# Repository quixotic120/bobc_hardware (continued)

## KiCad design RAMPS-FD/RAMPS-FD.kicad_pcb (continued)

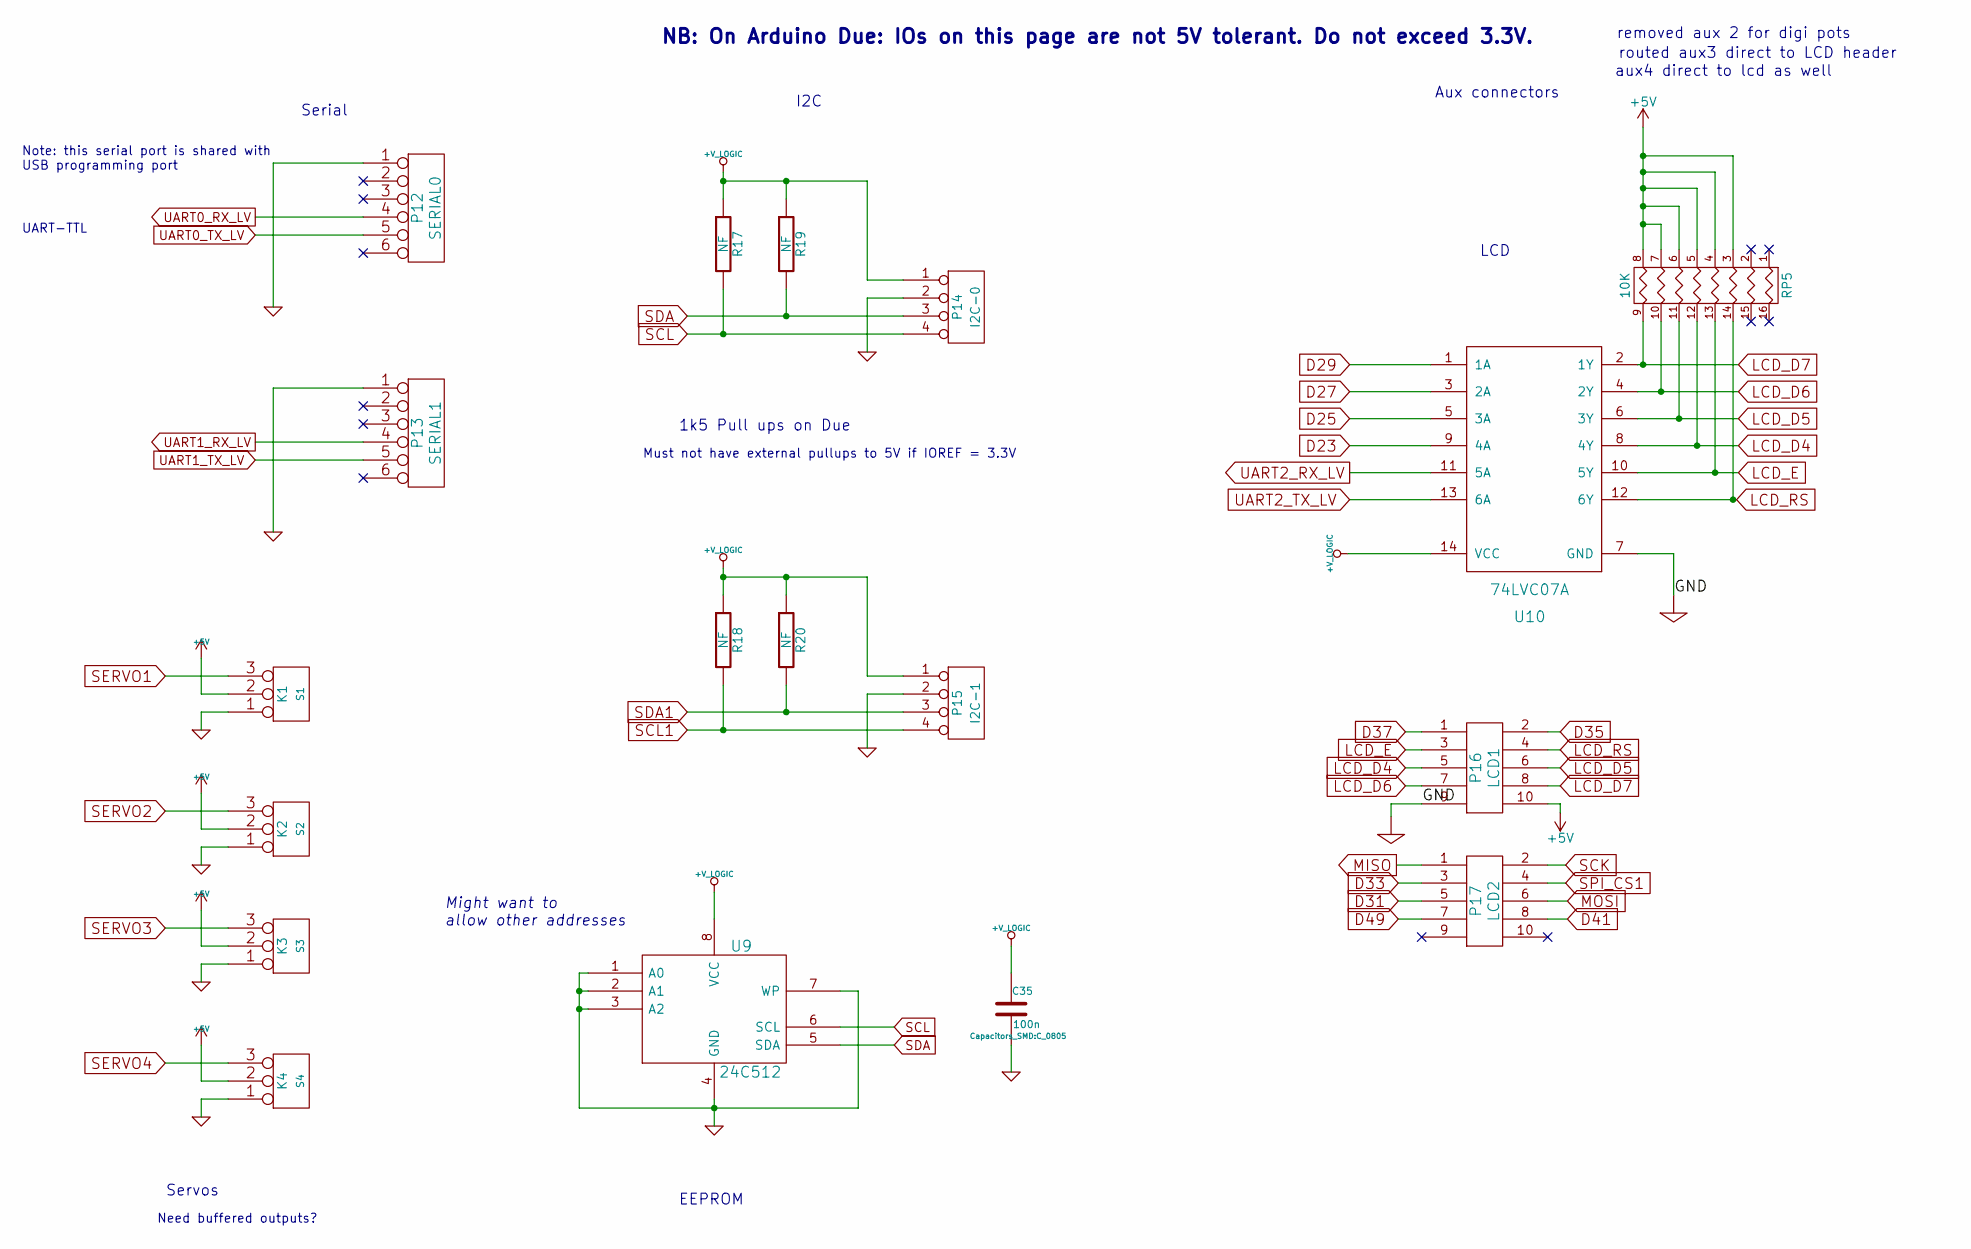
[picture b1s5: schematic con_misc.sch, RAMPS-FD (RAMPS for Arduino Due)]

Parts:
C35: 100n; C_0805
K1: S1; Pin_Header_Straight_1x03
K2: S2; Pin_Header_Straight_1x03
K3: S3; Pin_Header_Straight_1x03
K4: S4; Pin_Header_Straight_1x03
P12: SERIAL0; Pin_Header_Straight_1x06
P13: SERIAL1; Pin_Header_Straight_1x06
P14: I2C-0; Pin_Header_Straight_1x04
P15: I2C-1; Pin_Header_Straight_1x04
P16: LCD1; Pin_Header_Straight_2x05
P17: LCD2; Pin_Header_Straight_2x05
R17, R18, R19, R20: NF; R_0805
RP5: 10K; R_Cat16-8
U9: 24C512; SOIC-8-1EP_3.9x4.9mm_Pitch1.27mm
U10: 74LVC07A; TSSOP-14_4.4x5mm_Pitch0.65mm

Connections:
D23: U10.9 (4A); also elsewhere on the board
D25: U10.5 (3A); also elsewhere on the board
D27: U10.3 (2A); also elsewhere on the board
D29: U10.1 (1A); also elsewhere on the board
D31: P17.5; also elsewhere on the board
D33: P17.3; also elsewhere on the board
D35: P16.2; also elsewhere on the board
D37: P16.1; also elsewhere on the board
D41: P17.8; also elsewhere on the board
D49: P17.7; also elsewhere on the board
FD_5V: K1.2 (PM), K2.2 (PM), K3.2 (PM), K4.2 (PM), P16.10, RP5.3, RP5.4, RP5.5, RP5.6, RP5.7, RP5.8; also elsewhere on the board
LCD_D4: P16.5, RP5.12 (R5), U10.8 (4Y)
LCD_D5: P16.6, RP5.11 (R6), U10.6 (3Y)
LCD_D6: P16.7, RP5.10 (R7), U10.4 (2Y)
LCD_D7: P16.8, RP5.9 (R8), U10.2 (1Y)
LCD_E: P16.3, RP5.13 (R4), U10.10 (5Y)
LCD_RS: P16.4, RP5.14 (R3), U10.12 (6Y)
MISO: P17.1; also elsewhere on the board
MOSI: P17.6; also elsewhere on the board
SCK: P17.2; also elsewhere on the board
SCL: P14.4, R17.2, U9.6 (SCL); also elsewhere on the board
SCL1: P15.4, R18.2; also elsewhere on the board
SDA: P14.3, R19.2, U9.5 (SDA); also elsewhere on the board
SDA1: P15.3, R20.2; also elsewhere on the board
SERVO1: K1.3; also elsewhere on the board
SERVO2: K2.3; also elsewhere on the board
SERVO3: K3.3; also elsewhere on the board
SERVO4: K4.3; also elsewhere on the board
SPI_CS1: P17.4; also elsewhere on the board
UART0_RX_LV: P12.4; also elsewhere on the board
UART0_TX_LV: P12.5; also elsewhere on the board
UART1_RX_LV: P13.4; also elsewhere on the board
UART1_TX_LV: P13.5; also elsewhere on the board
UART2_RX_LV: U10.11 (5A); also elsewhere on the board
UART2_TX_LV: U10.13 (6A); also elsewhere on the board

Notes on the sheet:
Serial
UART-TTL
Need buffered outputs?
Must not have external pullups to 5V if IOREF = 3.3V
1k5 Pull ups on Due
Aux connectors
Servos
I2C
NB: On Arduino Due: IOs on this page are not 5V tolerant. Do not exceed 3.3V.
Note: this serial port is shared with USB programming port
EEPROM
Might want to allow other addresses
removed aux 2 for digi pots
routed aux3 direct to LCD header
aux4 direct to lcd as well
LCD

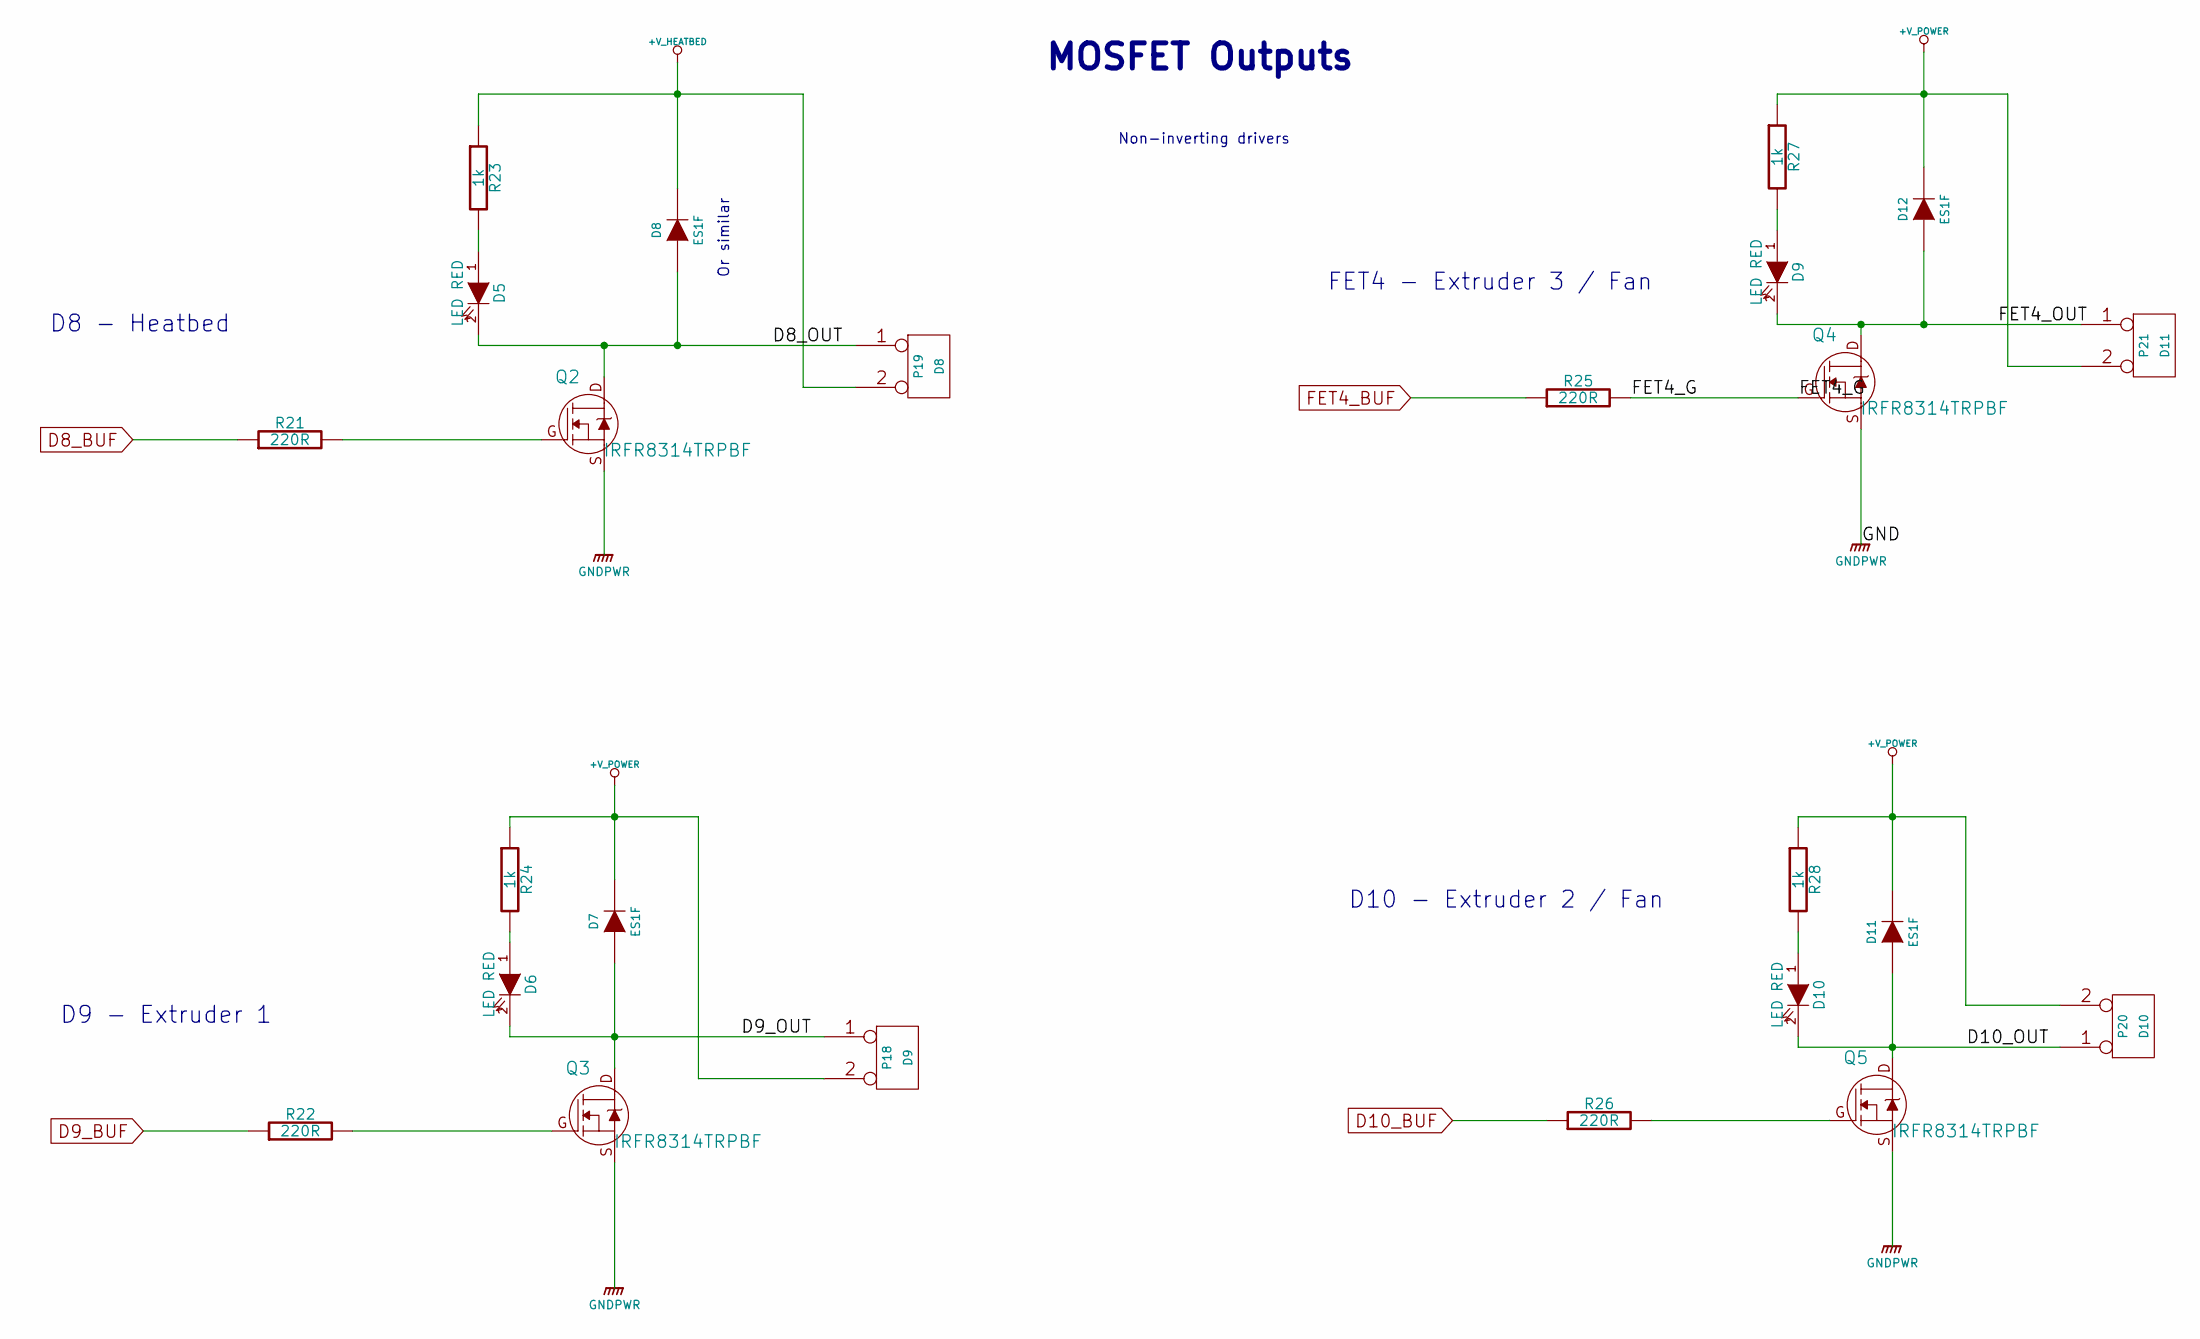
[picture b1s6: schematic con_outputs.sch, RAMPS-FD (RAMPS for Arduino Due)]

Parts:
D5, D6, D9, D10: LED RED; LED_0805
D7, D8, D11, D12: ES1F; DO-214AB
P18: D9; 2p-conn-5,08
P19: D8; 2p-conn-5,08
P20: D10; 2p-conn-5,08
P21: D11; 2p-conn-5,08
Q2, Q3, Q4, Q5: IRFR8314TRPBF; TO-252-2Lead_GDS
R21, R22, R25, R26: 220R; R_0805
R23, R24, R27, R28: 1k; R_0805

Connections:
+V_HEATBED: D8.2 (K), P19.2 (PM), R23.1; also elsewhere on the board
+V_POWER: D7.2 (K), D11.2 (K), D12.2 (K), P18.2 (PM), P20.2 (PM), P21.2 (PM), R24.1, R27.1, R28.1; also elsewhere on the board
/Mosfet Outputs/D8_OUT: D5.2 (K), D8.1 (A), P19.1, Q2.D
/Mosfet Outputs/D9_OUT: D6.2 (K), D7.1 (A), P18.1, Q3.D
/Mosfet Outputs/D10_OUT: D10.2 (K), D11.1 (A), P20.1, Q5.D
/Mosfet Outputs/FET4_G: Q4.G, R25.2
/Mosfet Outputs/FET4_OUT: D9.2 (K), D12.1 (A), P21.1, Q4.D
D8_BUF: R21.1; also elsewhere on the board
D9_BUF: R22.1; also elsewhere on the board
D10_BUF: R26.1; also elsewhere on the board
FET4_BUF: R25.1; also elsewhere on the board
unnamed: D5.1 (A), R23.2
unnamed: D6.1 (A), R24.2
unnamed: D9.1 (A), R27.2
unnamed: D10.1 (A), R28.2
unnamed: Q2.G, R21.2
unnamed: Q3.G, R22.2
unnamed: Q5.G, R26.2

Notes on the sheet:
FET4 - Extruder 3 / Fan
D10 - Extruder 2 / Fan
D9 - Extruder 1
D8 - Heatbed
Non-inverting drivers
MOSFET Outputs
Or similar

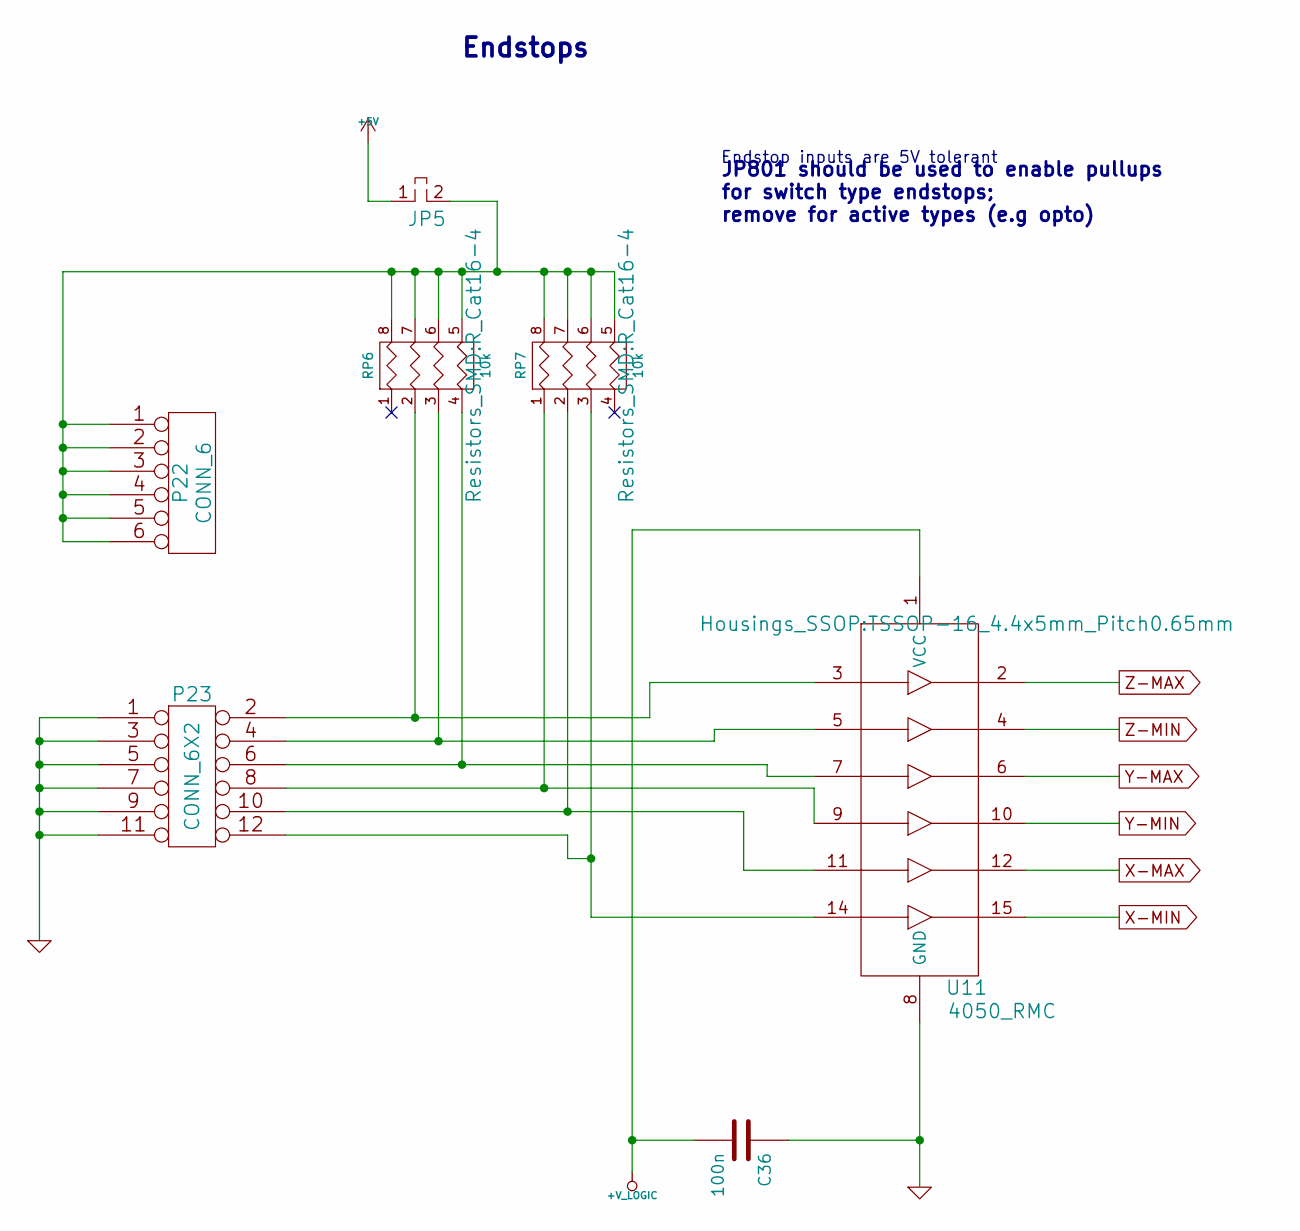
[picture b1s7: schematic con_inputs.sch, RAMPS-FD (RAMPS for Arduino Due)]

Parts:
C36: 100n; C_0805
JP5: JUMP_MINI; Pin_Header_Straight_1x02
P22: CONN_6; Pin_Header_Straight_1x06
P23: CONN_6X2; Pin_Header_Straight_2x06
RP6, RP7: 10k; R_Cat16-4
U11: 4050_RMC; TSSOP-16_4.4x5mm_Pitch0.65mm

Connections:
FD_5V: JP5.1; also elsewhere on the board
unnamed: JP5.2, P22.1, P22.2, P22.3, P22.4, P22.5, P22.6, RP6.5 (R4), RP6.6 (R3), RP6.7 (R2), RP6.8 (R1), RP7.5 (R4), RP7.6 (R3), RP7.7 (R2), RP7.8 (R1)
unnamed: P23.2, RP6.2, U11.3
unnamed: P23.4, RP6.3, U11.5
unnamed: P23.6, RP6.4, U11.7
unnamed: P23.8, RP7.1, U11.9
unnamed: P23.10, RP7.2, U11.11
unnamed: P23.12, RP7.3, U11.14
X-MAX: U11.12; also elsewhere on the board
X-MIN: U11.15; also elsewhere on the board
Y-MAX: U11.6; also elsewhere on the board
Y-MIN: U11.10; also elsewhere on the board
Z-MAX: U11.2; also elsewhere on the board
Z-MIN: U11.4; also elsewhere on the board

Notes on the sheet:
Endstop inputs are 5V tolerant
Endstops
JP801 should be used to enable pullups for switch type endstops; remove for active types (e.g opto)

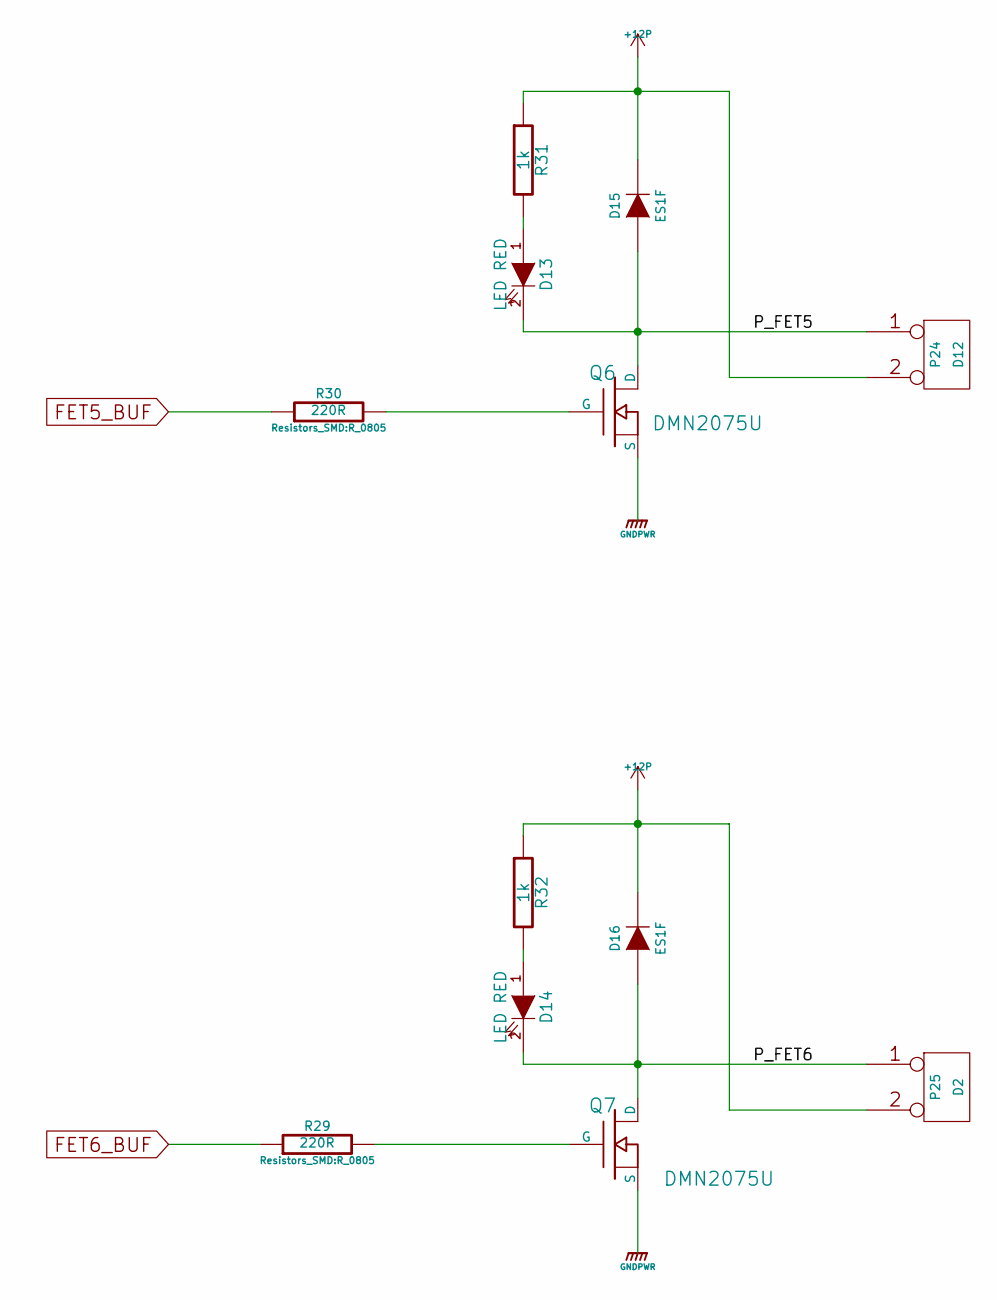
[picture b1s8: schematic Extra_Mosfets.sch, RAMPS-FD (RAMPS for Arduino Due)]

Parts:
D13, D14: LED RED; LED_0805
D15, D16: ES1F; DO-214AB
P24: D12; Socket_MOLEX-KK-RM2-54mm_Lock_2pin_straight
P25: D2; Socket_MOLEX-KK-RM2-54mm_Lock_2pin_straight
Q6, Q7: DMN2075U; SOT-23_GDS
R29, R30: 220R; R_0805
R31, R32: 1k; R_0805

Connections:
+12P: D15.2 (K), D16.2 (K), P24.2 (PM), P25.2 (PM), R31.1, R32.1; also elsewhere on the board
/Extra MOSFETs/P_FET5: D13.2 (K), D15.1 (A), P24.1, Q6.D
/Extra MOSFETs/P_FET6: D14.2 (K), D16.1 (A), P25.1, Q7.D
FET5_BUF: R30.1; also elsewhere on the board
FET6_BUF: R29.1; also elsewhere on the board
unnamed: D13.1 (A), R31.2
unnamed: D14.1 (A), R32.2
unnamed: Q6.G, R30.2
unnamed: Q7.G, R29.2

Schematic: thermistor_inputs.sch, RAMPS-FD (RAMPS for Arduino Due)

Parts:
C37, C38, C39, C40: 100n; C_0805
C41, C42, C43, C44: 10u; C_0805
C45: 10u; c_elec_4x5.3
D17, D18, D19, D20, D21, D22, D23, D24: 1N4148; SOD-323
P26: CONN_4X2; Pin_Header_Straight_2x04
R33, R34, R35, R36, R37, R39, R40, R43: 1k; R_0805
R38: 1K; R_0805
R41: 10k; R_0805
R42: 1k5; R_0805
U12: TL431_SOT23_RMC; SOT-23

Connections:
+12P: R41.1; also elsewhere on the board
GNDA: P26.1, P26.3, P26.5, P26.7; also elsewhere on the board
unnamed: P26.2, R33.2, R38.1
unnamed: P26.4, R34.2, R40.1
unnamed: P26.6, R35.2, R39.1
unnamed: P26.8, R36.2, R37.1
unnamed: R42.2, R43.1, U12.1 (R)
OV_REF: C45.1, D17.2 (K), D19.2 (K), D21.2 (K), D23.2 (K), R41.2, R42.1, U12.2 (K)
THERM0: C37.1, C41.1, D21.1 (A), D22.2 (K), R38.2; also elsewhere on the board
THERM1: C38.1, C42.1, D23.1 (A), D24.2 (K), R40.2; also elsewhere on the board
THERM2: C39.1, C43.1, D17.1 (A), D18.2 (K), R39.2; also elsewhere on the board
THERM3: C40.1, C44.1, D19.1 (A), D20.2 (K), R37.2; also elsewhere on the board

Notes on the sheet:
To CPU
From thermistor
Thermistor Inputs
Limit at 3.1V
Vref = 1.24V

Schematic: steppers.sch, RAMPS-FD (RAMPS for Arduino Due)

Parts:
C46, C50, C54, C57, C58, C61, C62, C68, C71: 100n/50v; C_0805
C47, C52, C65: 4u7/10v; C_0805
C48, C53, C66: 100u/35v; c_elec_6.3x7.7
C49, C67, C73: 100n50v; C_0805
C51, C63, C72: 470n/10v; C_0805
C55, C59, C69: 22n/50v; C_0805
C56, C60, C70: 1u/50v; C_0805
C64: 0.1u; C_0805
P27: Y-MOT; Socket_MOLEX-KK-RM2-54mm_Lock_4pin_straight
P28: Z-MOT1; Socket_MOLEX-KK-RM2-54mm_Lock_4pin_straight
P29: X-MOT; Socket_MOLEX-KK-RM2-54mm_Lock_4pin_straight
P30: Z-MOT2; Socket_MOLEX-KK-RM2-54mm_Lock_4pin_straight
P34: Y_SPRD_En; Pin_Header_Straight_1x02
P35: Z_SPRD_En; Pin_Header_Straight_1x02
P36: X_SPRD_En; Pin_Header_Straight_1x02
R44, R45, R50: 2r2; R_0805
R46, R47, R48, R49, R53, R54: 0r11; R_0805
R51, R52: 4k7; R_0805
U13, U14, U16: TMC2130; QFN-36-1EP_5x6mm_Pitch0.5mm
U15: DS3904; MSOP-8-1EP_3x3mm_Pitch0.65mm
W4: Y_REF; SolderWirePad_single_0-8mmDrill
W5: Z_REF; SolderWirePad_single_0-8mmDrill
W6: X_REF; SolderWirePad_single_0-8mmDrill
WXD7: XD0; SolderWirePad_single_0-8mmDrill
WXD8: XD1; SolderWirePad_single_0-8mmDrill
WYD1: YD0; SolderWirePad_single_0-8mmDrill
WYD2: YD1; SolderWirePad_single_0-8mmDrill
WZd0: ZD0; SolderWirePad_single_0-8mmDrill
WzD1: ZD1; SolderWirePad_single_0-8mmDrill

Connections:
+V_MOTOR: C54.2, C56.2, C57.2, C58.2, C60.2, C61.2, C68.2, C70.2, C71.2, U13.16 (VS), U13.31 (VS), U14.16 (VS), U14.31 (VS), U16.16 (VS), U16.31 (VS); also elsewhere on the board
/X_EN_BUF: U16.22 (DRV_ENN_CFG6); also elsewhere on the board
/Y_EN_BUF: U13.22 (DRV_ENN_CFG6); also elsewhere on the board
/Z_EN_BUF: U14.22 (DRV_ENN_CFG6); also elsewhere on the board
FD_5V: C64.1, R51.2, R52.1, U15.3 (VCC); also elsewhere on the board
unnamed: C46.2, U13.8 (VCC_IO)
unnamed: C47.1, R44.1, U13.25 (5VOUT)
unnamed: C48.1, C49.2, U13.30 (VSA)
unnamed: C50.2, U14.8 (VCC_IO)
unnamed: C51.1, R45.2, U14.19 (ENCA_DCIN_CFG5), U14.26 (VCC)
unnamed: C52.1, R45.1, U14.25 (5VOUT)
unnamed: C53.1, C73.2, U14.30 (VSA)
unnamed: C55.1, U13.28 (CPI)
unnamed: C55.2, U13.27 (CPO)
unnamed: C57.1, U13.29 (VCP)
unnamed: C59.1, U14.28 (CPI)
unnamed: C59.2, U14.27 (CPO)
unnamed: C61.1, U14.29 (VCP)
unnamed: C62.2, U16.8 (VCC_IO)
unnamed: C63.1, R50.2, U16.19 (ENCA_DCIN_CFG5), U16.26 (VCC)
unnamed: C65.1, R50.1, U16.25 (5VOUT)
unnamed: C66.1, C67.2, U16.30 (VSA)
unnamed: C69.1, U16.28 (CPI)
unnamed: C69.2, U16.27 (CPO)
unnamed: C71.1, U16.29 (VCP)
unnamed: C72.1, R44.2, U13.19 (ENCA_DCIN_CFG5), U13.26 (VCC)
unnamed: P27.1, U13.15 (OB2)
unnamed: P27.2, U13.32 (OA2)
unnamed: P27.3, U13.34 (OA1)
unnamed: P27.4, U13.13 (OB1)
unnamed: P28.1, P30.1, U14.15 (OB2)
unnamed: P28.2, P30.2, U14.32 (OA2)
unnamed: P28.3, P30.3, U14.34 (OA1)
unnamed: P28.4, P30.4, U14.13 (OB1)
unnamed: P29.1, U16.15 (OB2)
unnamed: P29.2, U16.32 (OA2)
unnamed: P29.3, U16.34 (OA1)
unnamed: P29.4, U16.13 (OB1)
unnamed: P34.1, U13.4 (SDI_NAI_CFG1)
unnamed: P35.1, U14.4 (SDI_NAI_CFG1)
unnamed: P36.1, U16.4 (SDI_NAI_CFG1)
unnamed: R46.1, U13.14 (BRB)
unnamed: R47.1, U13.33 (BRA)
unnamed: R48.1, U14.14 (BRB)
unnamed: R49.1, U14.33 (BRA)
unnamed: R53.1, U16.14 (BRB)
unnamed: R54.1, U16.33 (BRA)
unnamed: U13.20 (SWN_DIAG0), WYD1.1
unnamed: U13.21 (SWP_DIAG1), WYD2.1
unnamed: U14.20 (SWN_DIAG0), WZd0.1
unnamed: U14.21 (SWP_DIAG1), WzD1.1
unnamed: U16.20 (SWN_DIAG0), WXD7.1
unnamed: U16.21 (SWP_DIAG1), WXD8.1
SCL: R51.1, U15.2 (SCL); also elsewhere on the board
SDA: R52.2, U15.1 (SDA); also elsewhere on the board
X_DIR: U16.7 (REFR_DIR); also elsewhere on the board
X_STEP: U16.6 (REFL_STEP); also elsewhere on the board
X_TRIM: U15.7 (H0), U16.23 (AIN_IREF), W6.1
Y_DIR: U13.7 (REFR_DIR); also elsewhere on the board
Y_STEP: U13.6 (REFL_STEP); also elsewhere on the board
Y_TRIM: U13.23 (AIN_IREF), U15.6 (H1), W4.1
Z_DIR: U14.7 (REFR_DIR); also elsewhere on the board
Z_STEP: U14.6 (REFL_STEP); also elsewhere on the board
Z_TRIM: U14.23 (AIN_IREF), U15.5 (H2), W5.1

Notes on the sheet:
X AXIS
Y AXIS
Z AXIS

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
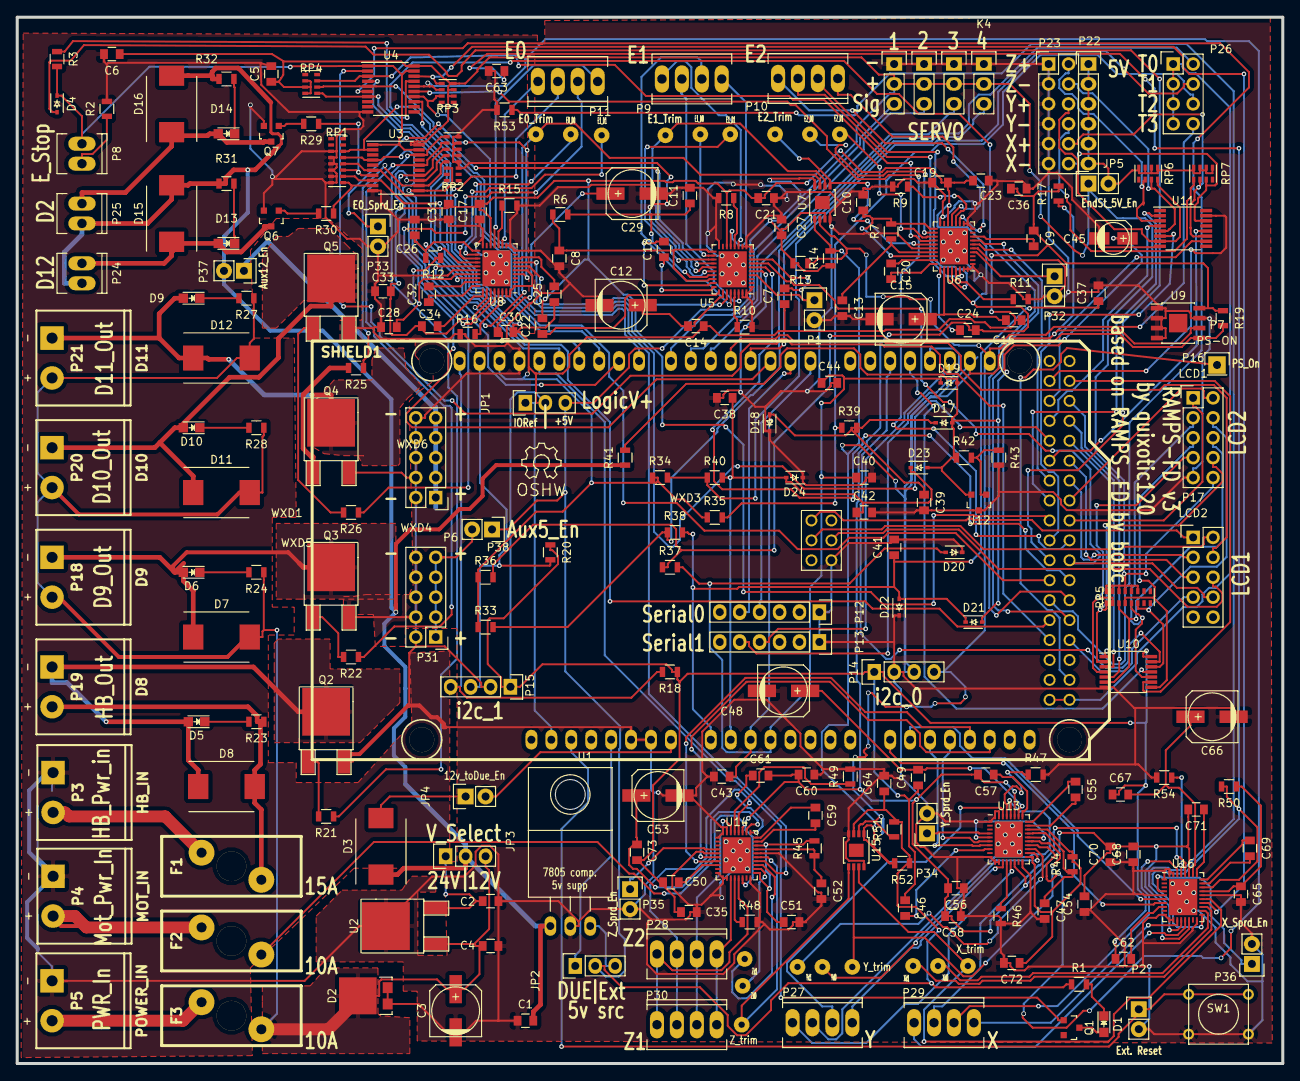
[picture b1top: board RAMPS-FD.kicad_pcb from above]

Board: 2 copper layers, 161.3 x 133.3 mm, 250 parts (0 on the bottom side), 239 nets.

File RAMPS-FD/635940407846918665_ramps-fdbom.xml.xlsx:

Reference | Value | Footprint | Count | Note
SHIELD1 | ARDUINO_DUE_SHIELD | arduinodue:ARDUINO_DUE_RAMPS_SHIELD | 1
SW1 | RESET | Buttons_Switches_ThroughHole:SW_PUSH_SMALL | 1
D1 | LED GRN | LEDs:LED_0805 | 1
R1 | 330R | Resistors_SMD:R_0805 | 1
P2 | RESET | Pin_Headers:Pin_Header_Straight_1x02 | 1
Q1 | 2N7002 | TO_SOT_Packages_SMD:SOT-23_GDS | 1
LOGO1 | OPEN_HARDWARE_1 | Symbols:Symbol_OSHW-Logo_SilkScreen | 1
JP3 | VSEL | Pin_Headers:Pin_Header_Straight_1x03 | 1
JP4 | VIN | Pin_Headers:Pin_Header_Straight_1x02 | 1
P5 | POWER_IN | RAMPS-FD v3:2p-conn-5,08 | 1
P3 | HB_IN | RAMPS-FD v3:2p-conn-5,08 | 1
JP1 | VLOG | Pin_Headers:Pin_Header_Straight_1x03 | 1
F2;F3 | FUSE 10A | RAMPS-FD v3:FUSE-MINI-AUTO | 2
P4 | MOT_IN | RAMPS-FD v3:2p-conn-5,08 | 1
P7 | PS-ON | Pin_Headers:Pin_Header_Straight_1x01 | 1
C4 | 100n 35V | Capacitors_SMD:C_0805 | 1
C3 | 100u 35V | Capacitors_SMD:c_elec_6.3x7.7 | 1
D3;D8;D12;D7;D11;D15;D16 | ES1F | Diodes_SMD:DO-214AB | 7
F1 | FUSE 15A | RAMPS-FD v3:FUSE-MINI-AUTO | 1
U2 | LM7812 | TO_SOT_Packages_THT:TO-252-2Lead_edit | 1
C2 | 100n 16V | Capacitors_SMD:C_0805 | 1
D2 | SS10Pxx | TO_SOT_Packages_SMD:TO-277A | 1 | If = 10 A
U1 | oki-78sr-5h | TO_SOT_Packages_THT:TO-220_Neutral123_Horizontal_OKI_Mod | 1
C1 | 22u/35v | Capacitors_SMD:C_0805 | 1
P31 | 5v aux | Pin_Headers:Pin_Header_Straight_2x05 | 1
P6 | 12V aux | Pin_Headers:Pin_Header_Straight_2x05 | 1
JP2 | 5V_SEL | Pin_Headers:Pin_Header_Straight_1x03 | 1
U4;U3 | 74ACT244 | Housings_SSOP:TSSOP-20_4.4x6.5mm_Pitch0.65mm | 2
C6;C5;C35;C36;C37;C38;C39;C40 | 100n | Capacitors_SMD:C_0805 | 8
D4;D22;D21;D23;D24;D18;D17;D19;D20 | 1N4148 | Diodes_SMD:SOD-323 | 9
R2;R13;R14;R51;R52 | 4k7 | Resistors_SMD:R_0805 | 5
P8 | ESTOP | Sockets_MOLEX_KK-System:Socket_MOLEX-KK-RM2-54mm_Lock_2pin_straight | 1
R3 | 100k | Resistors_SMD:R_0805 | 1
RP1;RP2 | R_PACK8 | Resistors_SMD:R_Cat16-8 | 2
RP4;RP3 | R_PACK4 | Resistors_SMD:R_Cat16-4 | 2
P11 | E0-MOT | Sockets_MOLEX_KK-System:Socket_MOLEX-KK-RM2-54mm_Lock_4pin_straight | 1
U8;U5;U6;U16;U13;U14 | TMC2130 | Housings_DFN_QFN:QFN-36-1EP_5x6mm_Pitch0.5mm | 6
C31;C34;C25;C17;C22;C7;C19;C24;C9;C68;C71;C62;C54;C57;C46;C58;C61;C50 | 100n/50v | Capacitors_SMD:C_0805 | 18
C33;C21;C23;C70;C56;C60 | 1u/50v | Capacitors_SMD:C_0805 | 6
C32;C18;C20;C69;C55;C59 | 22n/50v | Capacitors_SMD:C_0805 | 6
R16;R15;R10;R8;R11;R9;R54;R53;R47;R46;R49;R48 | 0r11 | Resistors_SMD:R_0805 | 12
R12;R6;R7;R50;R44;R45 | 2r2 | Resistors_SMD:R_0805 | 6
C30;C14;C16;C67;C49;C73 | 100n50v | Capacitors_SMD:C_0805 | 6
C28;C11;C13;C65;C47;C52 | 4u7/10v | Capacitors_SMD:C_0805 | 6
C26;C8;C10;C63;C72;C51 | 470n/10v | Capacitors_SMD:C_0805 | 6
C29;C12;C15;C66;C48;C53 | 100u/35v | Capacitors_SMD:c_elec_6.3x7.7 | 6
WXD6 | E0D1 | Wire_Pads:SolderWirePad_single_0-8mmDrill | 1
WXD5 | E0D0 | Wire_Pads:SolderWirePad_single_0-8mmDrill | 1
U7;U15 | DS3904 | Housings_SSOP:MSOP-8-1EP_3x3mm_Pitch0.65mm | 2
C27;C64 | 0.1u | Capacitors_SMD:C_0805 | 2
W3 | E0_REF | Wire_Pads:SolderWirePad_single_0-8mmDrill | 1
P9 | E1-MOT | Sockets_MOLEX_KK-System:Socket_MOLEX-KK-RM2-54mm_Lock_4pin_straight | 1
WXD2 | E1D1 | Wire_Pads:SolderWirePad_single_0-8mmDrill | 1
WXD1 | E1D0 | Wire_Pads:SolderWirePad_single_0-8mmDrill | 1
W1 | E1_REF | Wire_Pads:SolderWirePad_single_0-8mmDrill | 1
P10 | E2-MOT | Sockets_MOLEX_KK-System:Socket_MOLEX-KK-RM2-54mm_Lock_4pin_straight | 1
WXD4 | E2D1 | Wire_Pads:SolderWirePad_single_0-8mmDrill | 1
WXD3 | E2D0 | Wire_Pads:SolderWirePad_single_0-8mmDrill | 1
W2 | E2_REF | Wire_Pads:SolderWirePad_single_0-8mmDrill | 1
P33 | E0_SPRD_En | Pin_Headers:Pin_Header_Straight_1x02 | 1
P1 | E1_SPRD_En | Pin_Headers:Pin_Header_Straight_1x02 | 1
P32 | E2_SPRD_En | Pin_Headers:Pin_Header_Straight_1x02 | 1
P15 | I2C-1 | Pin_Headers:Pin_Header_Straight_1x04 | 1
R20;R18;R17;R19 | NF | Resistors_SMD:R_0805 | 4
P13 | SERIAL1 | Pin_Headers:Pin_Header_Straight_1x06 | 1
P12 | SERIAL0 | Pin_Headers:Pin_Header_Straight_1x06 | 1
K4 | S4 | Pin_Headers:Pin_Header_Straight_1x04 | 1
K3 | S3 | Pin_Headers:Pin_Header_Straight_1x04 | 1
K2 | S2 | Pin_Headers:Pin_Header_Straight_1x04 | 1
K1 | S1 | Pin_Headers:Pin_Header_Straight_1x04 | 1
P14 | I2C-0 | Pin_Headers:Pin_Header_Straight_1x04 | 1
U9 | 24C512 | Housings_SOIC:SOIC-8-1EP_3.9x4.9mm_Pitch1.27mm | 1
P16 | LCD1 | Pin_Headers:Pin_Header_Straight_2x05 | 1
P17 | LCD2 | Pin_Headers:Pin_Header_Straight_2x05 | 1
RP5 | 10K | Resistors_SMD:R_Cat16-8 | 1
U10;U11 | 74LVC07A | Housings_SSOP:TSSOP-14_4.4x5mm_Pitch0.65mm | 2
P20 | D10 | RAMPS-FD v3:2p-conn-5,08 | 1
P18 | D9 | RAMPS-FD v3:2p-conn-5,08 | 1
P19 | D8 | RAMPS-FD v3:2p-conn-5,08 | 1
P21 | D11 | RAMPS-FD v3:2p-conn-5,08 | 1
D9;D6;D10;D5;D13;D14 | LED RED | LEDs:LED_0805 | 6
R27;R24;R28;R23;R31;R32;R40;R39;R37;R36;R35;R34;R33;R43 | 1k | Resistors_SMD:R_0805 | 14
Q4;Q2;Q3;Q5 | IRFR8314TRPBF | TO_SOT_Packages_SMD:TO-252-2Lead_GDS | 4
R21;R22;R26;R25;R30;R29 | 220R | Resistors_SMD:R_0805 | 6
RP6;RP7 | 10k | Resistors_SMD:R_Cat16-4 | 2
JP5 | JUMP_MINI | Pin_Headers:Pin_Header_Straight_1x02 | 1
P23 | CONN_6X2 | Pin_Headers:Pin_Header_Straight_2x06 | 1
P22 | CONN_6 | Pin_Headers:Pin_Header_Straight_1x06 | 1
Q6;Q7 | DMN2075U | TO_SOT_Packages_SMD:SOT-23_GDS | 2
P24 | D12 | Sockets_MOLEX_KK-System:Socket_MOLEX-KK-RM2-54mm_Lock_2pin_straight | 1
P25 | D2 | Sockets_MOLEX_KK-System:Socket_MOLEX-KK-RM2-54mm_Lock_2pin_straight | 1
R38 | 1K | Resistors_SMD:R_0805 | 1
C44;C43;C42;C41 | 10u | Capacitors_SMD:C_0805 | 4
P26 | CONN_4X2 | Pin_Headers:Pin_Header_Straight_2x04 | 1
R41 | 10k | Resistors_SMD:R_0805 | 1
R42 | 1k5 | Resistors_SMD:R_0805 | 1
C45 | 10u | Capacitors_SMD:c_elec_4x5.3 | 1
U12 | TL431_SOT23_RMC | TO_SOT_Packages_SMD:SOT-23 | 1
P28 | Z-MOT1 | Sockets_MOLEX_KK-System:Socket_MOLEX-KK-RM2-54mm_Lock_4pin_straight | 1
P27 | Y-MOT | Sockets_MOLEX_KK-System:Socket_MOLEX-KK-RM2-54mm_Lock_4pin_straight | 1
P29 | X-MOT | Sockets_MOLEX_KK-System:Socket_MOLEX-KK-RM2-54mm_Lock_4pin_straight | 1
WXD8 | XD1 | Wire_Pads:SolderWirePad_single_0-8mmDrill | 1
WXD7 | XD0 | Wire_Pads:SolderWirePad_single_0-8mmDrill | 1
WYD2 | YD1 | Wire_Pads:SolderWirePad_single_0-8mmDrill | 1
WYD1 | YD0 | Wire_Pads:SolderWirePad_single_0-8mmDrill | 1
WzD1 | ZD1 | Wire_Pads:SolderWirePad_single_0-8mmDrill | 1
WZd0 | ZD0 | Wire_Pads:SolderWirePad_single_0-8mmDrill | 1
W6 | X_REF | Wire_Pads:SolderWirePad_single_0-8mmDrill | 1
W4 | Y_REF | Wire_Pads:SolderWirePad_single_0-8mmDrill | 1
W5 | Z_REF | Wire_Pads:SolderWirePad_single_0-8mmDrill | 1
P30 | Z-MOT2 | Sockets_MOLEX_KK-System:Socket_MOLEX-KK-RM2-54mm_Lock_4pin_straight | 1
P36 | X_SPRD_En | Pin_Headers:Pin_Header_Straight_1x02 | 1
P34 | Y_SPRD_En | Pin_Headers:Pin_Header_Straight_1x02 | 1
P35 | Z_SPRD_En | Pin_Headers:Pin_Header_Straight_1x02 | 1

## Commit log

2016-05-14 ramps-FD variant
2016-05-14 ramps-FD
